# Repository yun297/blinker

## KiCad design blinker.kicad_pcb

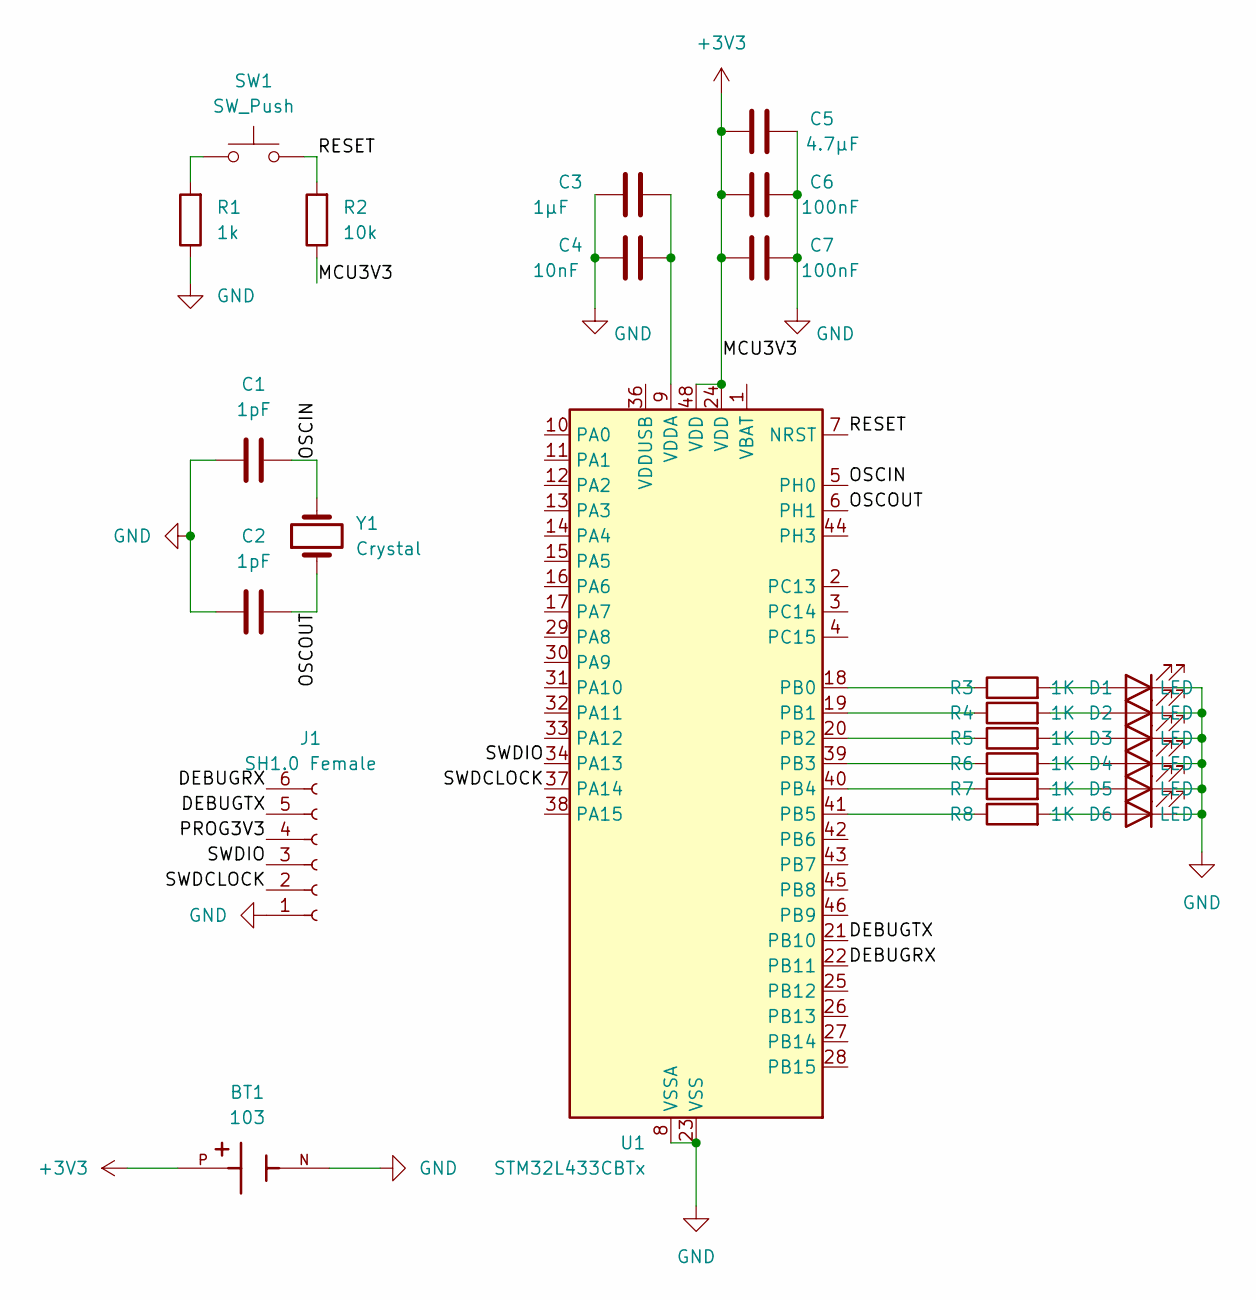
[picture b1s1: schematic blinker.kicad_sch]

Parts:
BT1: 103; BAT_103; PARTREV A
C1, C2: 1pF; C_0603_1608Metric
C3: 1µF; C_0603_1608Metric
C4: 10nF; C_0603_1608Metric
C5: 4.7µF; C_0603_1608Metric
C6, C7: 100nF; C_0603_1608Metric
D1, D2, D3, D4, D5, D6: LED; LED_0603_1608Metric
J1: SH1.0 Female; JST_SH_BM06B-SRSS-TB_1x06-1MP_P1.00mm_Vertical
R1: 1k; R_0603_1608Metric
R2: 10k; R_0603_1608Metric
R3, R4, R5, R6, R7, R8: 1K; R_0603_1608Metric
SW1: SW_Push; SW_Push_SPST_NO_Alps_SKRK
U1: STM32L433CBTx; LQFP-48_7x7mm_P0.5mm
Y1: Crystal; Crystal_SMD_5032-2Pin_5.0x3.2mm

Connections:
+3V3: C5.1, C6.1, C7.1, R2.1, U1.24 (VDD), U1.48 (VDD); also elsewhere on the board
/DEBUGRX: J1.6, U1.22 (PB11)
/DEBUGTX: J1.5, U1.21 (PB10)
/OSCIN: C1.2, U1.5 (PH0), Y1.2
/OSCOUT: C2.2, U1.6 (PH1), Y1.1
/PROG3V3: J1.4
/RESET: R2.2, SW1.2, U1.7 (NRST)
/SWDCLOCK: J1.2, U1.37 (PA14)
/SWDIO: J1.3, U1.34 (PA13)
GND: C1.1, C2.1, C3.2, C4.2, C5.2, C6.2, C7.2, D1.1 (K), D2.1 (K), D3.1 (K), D4.1 (K), D5.1 (K), D6.1 (K), J1.1, R1.1, U1.8 (VSSA), U1.23 (VSS), U1.35 (VSS), U1.47 (VSS); also elsewhere on the board
unnamed: D1.2 (A), R3.2
unnamed: D2.2 (A), R4.2
unnamed: D3.2 (A), R5.2
unnamed: D4.2 (A), R6.2
unnamed: D5.2 (A), R7.2
unnamed: D6.2 (A), R8.2
unnamed: R1.2, SW1.1
unnamed: R3.1, U1.18 (PB0)
unnamed: R4.1, U1.19 (PB1)
unnamed: R5.1, U1.20 (PB2)
unnamed: R6.1, U1.39 (PB3)
unnamed: R7.1, U1.40 (PB4)
unnamed: R8.1, U1.41 (PB5)
unnamed: C3.1, C4.1, U1.9 (VDDA)

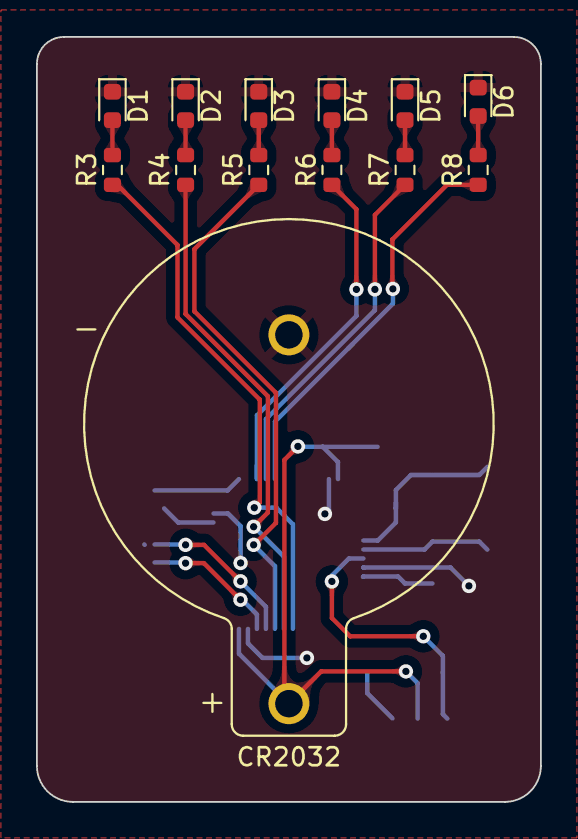
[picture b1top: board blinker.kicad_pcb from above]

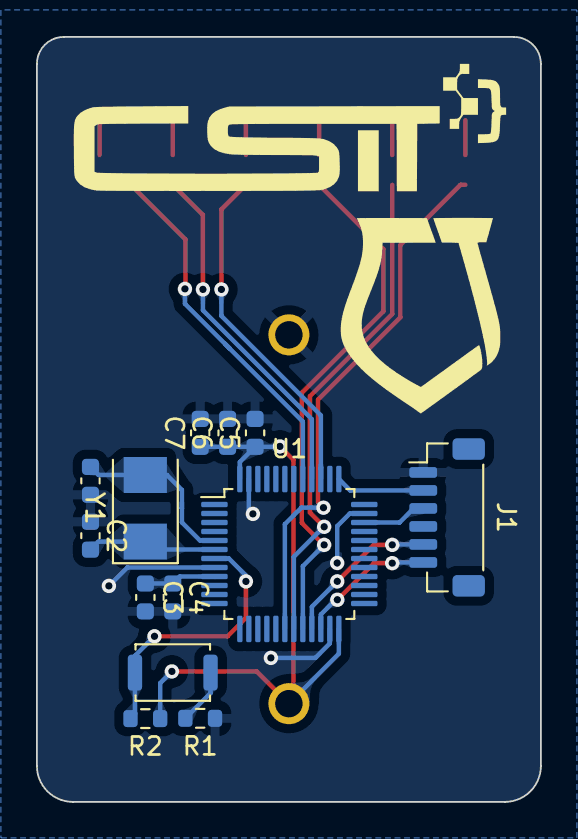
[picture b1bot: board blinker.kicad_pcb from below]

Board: 2 copper layers, 28.0 x 42.5 mm, 26 parts (13 on the bottom side), 23 nets.

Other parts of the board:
CR2032: CR2032; BAT_103

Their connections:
+3V3: CR2032.P; also elsewhere on the board
GND: CR2032.N; also elsewhere on the board

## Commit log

2024-10-16 dasd
2024-10-17 switch thingy
2024-10-17 battery holder schema
2024-10-17 gerber
2024-10-18 drc settings
